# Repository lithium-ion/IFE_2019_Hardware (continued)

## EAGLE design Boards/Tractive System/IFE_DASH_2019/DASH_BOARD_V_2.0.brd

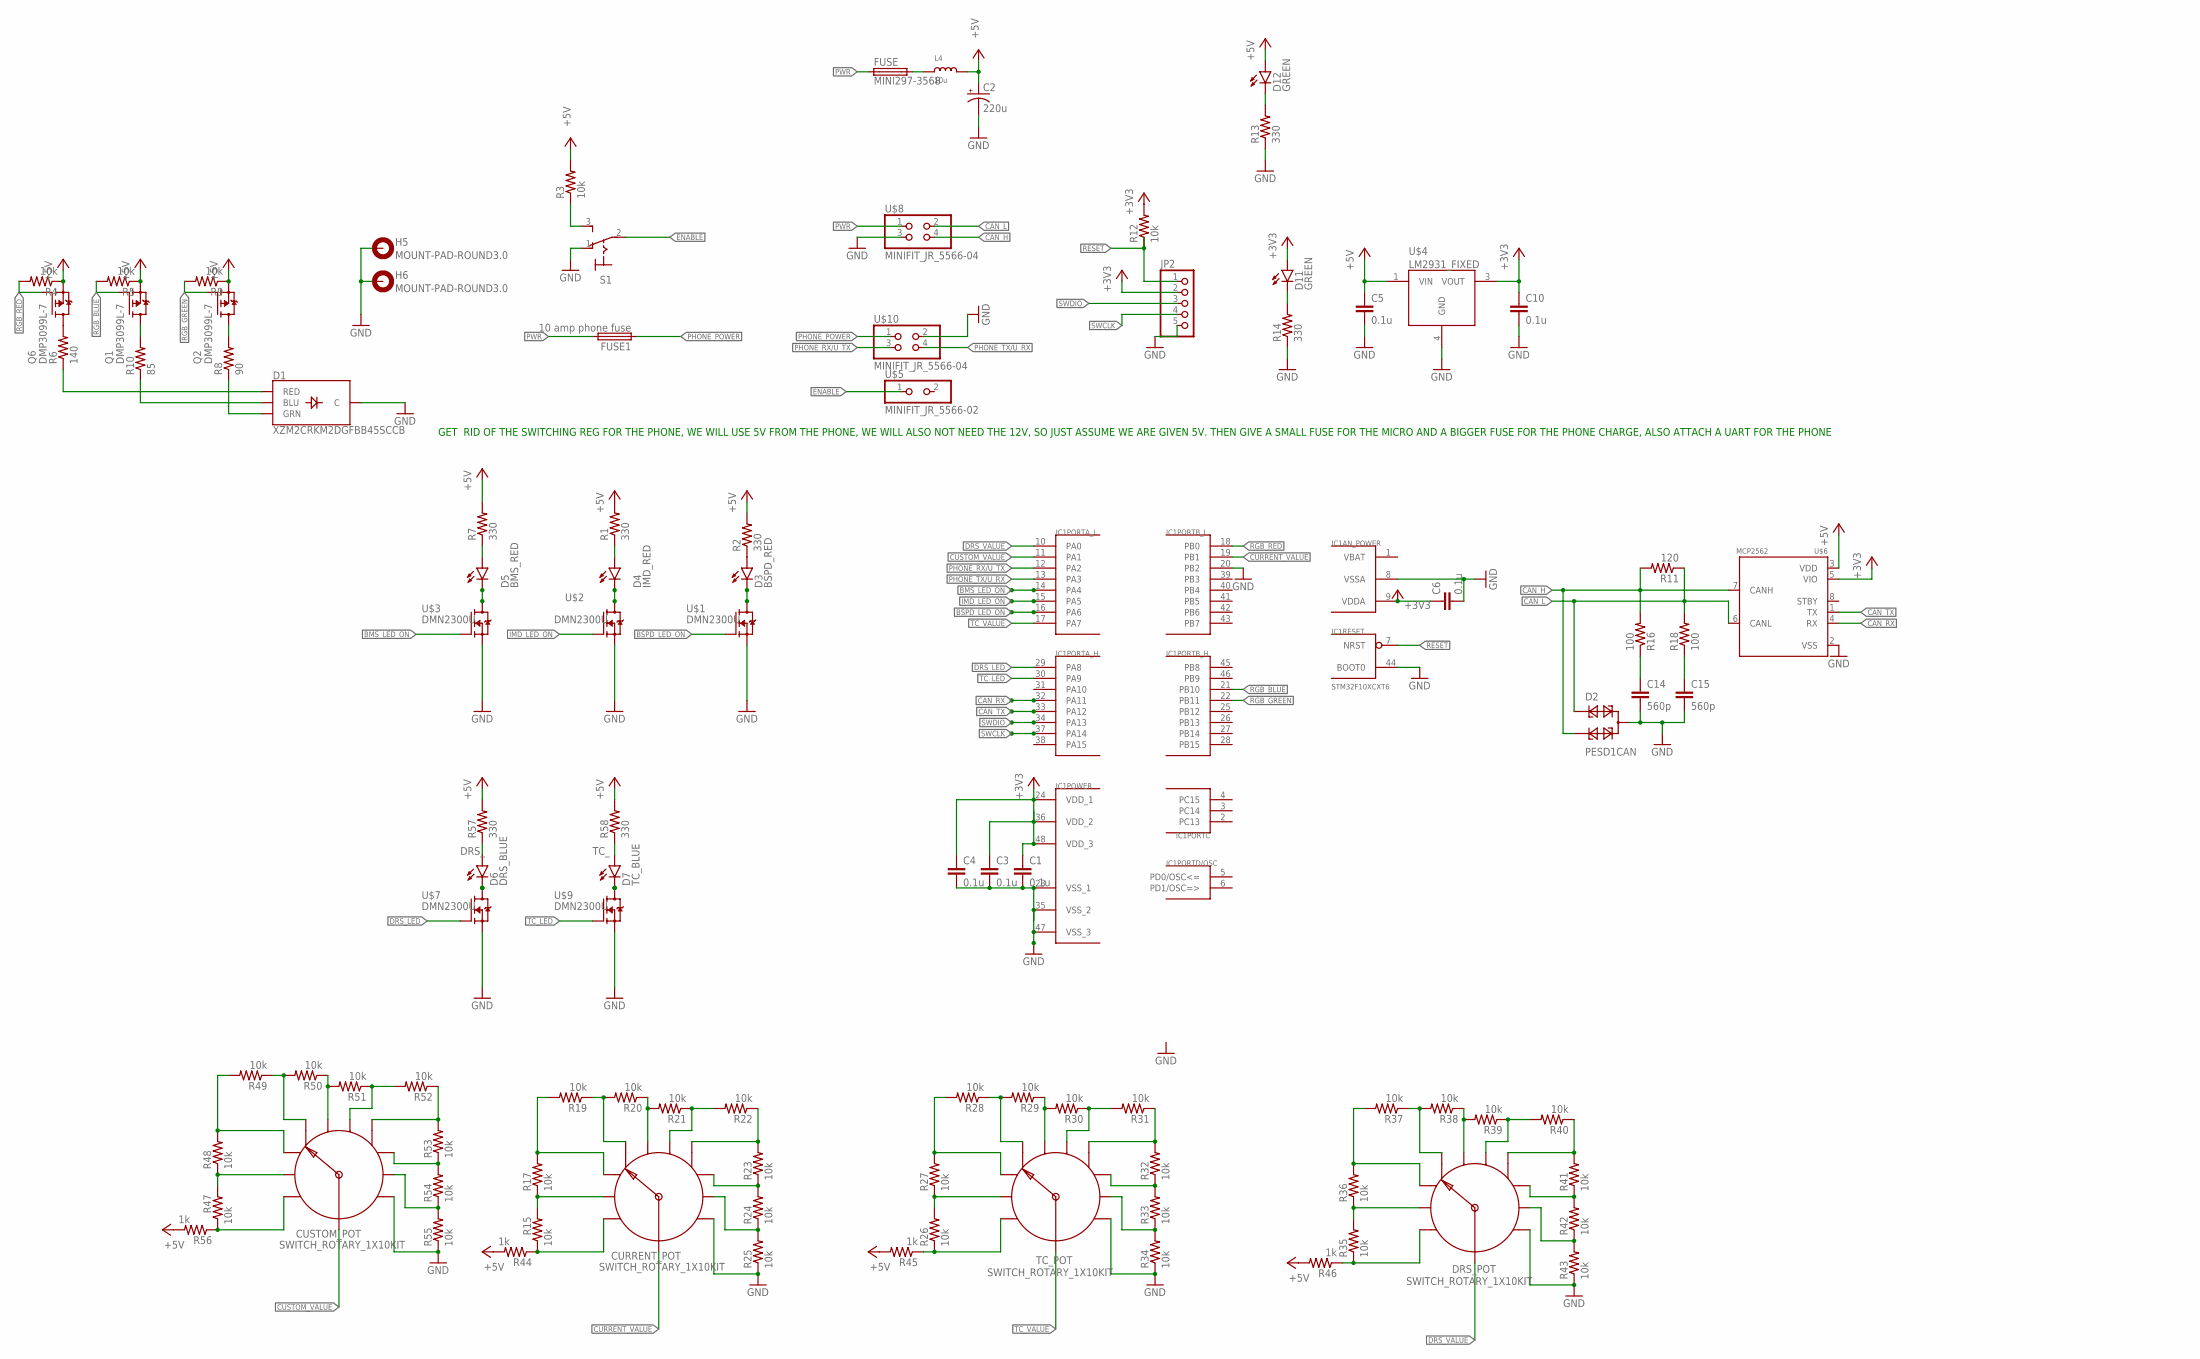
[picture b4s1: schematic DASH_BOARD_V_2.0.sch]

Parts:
C1, C3, C4, C5, C6, C10: 0.1u; C0805K
C2: 220u; E2,5-7
C14, C15: 560p; C0805K
CURRENT_POT: SWITCH_ROTARY_1X10KIT; ROTARY_SWITCH_1X10_KIT
CUSTOM_POT: SWITCH_ROTARY_1X10KIT; ROTARY_SWITCH_1X10_KIT
D1: XZM2CRKM2DGFBB45SCCB; PLCC4SMDLED
D2: PESD1CAN; SOT23
D3: BSPD_RED; LED-0603
D4: IMD_RED; LED-0603
D5: BMS_RED; LED-0603
D6: DRS_BLUE; LED-0603
D7: TC_BLUE; LED-0603
D11, D12: GREEN; LED-0603
DRS_POT: SWITCH_ROTARY_1X10KIT; ROTARY_SWITCH_1X10_KIT
FUSE: MINI297-3568; 3568
FUSE1: 10 amp phone fuse; 3568
H5, H6: MOUNT-PAD-ROUND3.0; 3,0-PAD
IC1: STM32F10XCXT6; TQFP48
JP2: PINHD-1X5; 1X05
L4: 10u; INDUCTOR_5X5MM_NR5040_NOTHERMALS
Q1, Q2, Q6: DMP3099L-7; SOT23
R1, R2, R7, R57, R58: 330; R0805
R3, R4, R5, R9, R12, R15, R17, R19, R20, R21, R22, R23, R24, R25, R26, R27, R28, R29, R30, R31, R32, R33, R34, R35, R36, R37, R38, R39, R40, R41, R42, R43, R47, R48, R49, R50, R51, R52, R53, R54, R55: 10k; R0805
R6: 140; R0805
R8: 90; R0805
R10: 85; R0805
R11: 120; R0805
R13, R14: 330; R0603
R16, R18: 100; R0805
R44, R45, R46, R56: 1k; R0805
S1: 320-916
TC_POT: SWITCH_ROTARY_1X10KIT; ROTARY_SWITCH_1X10_KIT
U$1, U$2, U$3, U$7, U$9: DMN2300U; SOT23
U$4: LM2931_FIXED; DPAK
U$5: MINIFIT_JR_5566-02
U$6: MCP2562; SOIC8
U$8, U$10: MINIFIT_JR_5566-04

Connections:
+3V3: C1.1, C3.1, C4.1, C6.1, C10.1, D11.A, IC1.9 (VDDA), IC1.24 (VDD_1), IC1.36 (VDD_2), IC1.48 (VDD_3), JP2.2, R12.2, U$4.3 (VOUT), U$6.5 (VIO)
+5V: C2.+, C5.1, D12.A, L4.P$2 (2), Q1.2 (S), Q2.2 (S), Q6.2 (S), R1.2, R2.2, R3.2, R4.1, R5.1, R7.2, R9.1, R44.2, R45.2, R46.2, R56.2, R57.2, R58.2, U$4.1 (VIN), U$6.3 (VDD)
BMS_LED: D5.A, R7.1
BMS_LED_ON: IC1.14 (PA4), U$3.1 (G)
BSPD_LED: D3.A, R2.1
BSPD_LED_ON: IC1.16 (PA6), U$1.1 (G)
CAN_H: D2.2, R11.2, R16.2, U$6.7 (CANH), U$8.4
CAN_L: D2.1, R11.1, R18.2, U$6.6 (CANL), U$8.2
CAN_RX: IC1.32 (PA11), U$6.4 (RX)
CAN_TX: IC1.33 (PA12), U$6.1 (TX)
CURRENT_VALUE: CURRENT_POT.COMMON, IC1.19 (PB1)
CUSTOM_VALUE: CUSTOM_POT.COMMON, IC1.11 (PA1)
DRS_: D6.A, R57.1
DRS_LED: IC1.29 (PA8), U$7.1 (G)
DRS_VALUE: DRS_POT.COMMON, IC1.10 (PA0)
ENABLE: S1.2, U$5.1
GND: C1.2, C2.-, C3.2, C4.2, C5.2, C6.2, C10.2, C14.2, C15.2, CURRENT_POT.10, CUSTOM_POT.10, D1.4 (C), D2.3, DRS_POT.10, H5.B3,0, H6.B3,0, IC1.8 (VSSA), IC1.20 (PB2), IC1.23 (VSS_1), IC1.35 (VSS_2), IC1.44 (BOOT0), IC1.47 (VSS_3), JP2.5, R13.1, R14.1, R25.1, R34.1, R43.1, R55.1, S1.1 (O), TC_POT.10, U$1.2 (S), U$2.2 (S), U$3.2 (S), U$4.4 (GND), U$6.2 (VSS), U$7.2 (S), U$8.3, U$9.2 (S), U$10.2
IMD_LED: D4.A, R1.1
IMD_LED_ON: IC1.15 (PA5), U$2.1 (G)
unnamed: Q6.3 (D), R6.2
unnamed: C14.1, R16.1
unnamed: D5.C, U$3.3 (D)
unnamed: R3.1, S1.3 (S)
unnamed: D1.2 (GRN), R8.1
unnamed: FUSE.P$2 (2), FUSE.P$3 (2), L4.P$1 (1)
unnamed: CURRENT_POT.2, R15.2, R17.1
unnamed: D4.C, U$2.3 (D)
unnamed: C15.1, R18.1
unnamed: D12.C, R13.2
unnamed: D11.C, R14.2
unnamed: D3.C, U$1.3 (D)
unnamed: CURRENT_POT.3, R17.2, R19.2
unnamed: CURRENT_POT.1, R15.1, R44.1
unnamed: D1.3 (BLU), R10.1
unnamed: D1.1 (RED), R6.1
unnamed: CURRENT_POT.4, R19.1, R20.2
unnamed: CURRENT_POT.5, R20.1, R21.2
unnamed: CURRENT_POT.6, R21.1, R22.2
unnamed: CURRENT_POT.7, R22.1, R23.2
unnamed: CURRENT_POT.8, R23.1, R24.2
unnamed: CURRENT_POT.9, R24.1, R25.2
unnamed: R26.1, R45.1, TC_POT.1
unnamed: Q1.3 (D), R10.2
unnamed: R26.2, R27.1, TC_POT.2
unnamed: R27.2, R28.2, TC_POT.3
unnamed: Q2.3 (D), R8.2
unnamed: R28.1, R29.2, TC_POT.4
unnamed: R29.1, R30.2, TC_POT.5
unnamed: R30.1, R31.2, TC_POT.6
unnamed: R31.1, R32.2, TC_POT.7
unnamed: R32.1, R33.2, TC_POT.8
unnamed: R33.1, R34.2, TC_POT.9
unnamed: CUSTOM_POT.2, R47.2, R48.1
unnamed: CUSTOM_POT.3, R48.2, R49.2
unnamed: DRS_POT.2, R35.2, R36.1
unnamed: DRS_POT.3, R36.2, R37.2
unnamed: DRS_POT.1, R35.1, R46.1
unnamed: DRS_POT.4, R37.1, R38.2
unnamed: DRS_POT.5, R38.1, R39.2
unnamed: DRS_POT.6, R39.1, R40.2
unnamed: DRS_POT.7, R40.1, R41.2
unnamed: DRS_POT.8, R41.1, R42.2
unnamed: DRS_POT.9, R42.1, R43.2
unnamed: CUSTOM_POT.4, R49.1, R50.2
unnamed: CUSTOM_POT.5, R50.1, R51.2
unnamed: CUSTOM_POT.6, R51.1, R52.2
unnamed: CUSTOM_POT.7, R52.1, R53.2
unnamed: CUSTOM_POT.8, R53.1, R54.2
unnamed: CUSTOM_POT.9, R54.1, R55.2
unnamed: CUSTOM_POT.1, R47.1, R56.1
unnamed: D6.C, U$7.3 (D)
unnamed: D7.C, U$9.3 (D)
PHONE_POWER: FUSE1.P$1 (1), FUSE1.P$4 (1), U$10.1
PHONE_RX/U_TX: IC1.12 (PA2), U$10.3
PHONE_TX/U_RX: IC1.13 (PA3), U$10.4
PWR: FUSE.P$1 (1), FUSE.P$4 (1), FUSE1.P$2 (2), FUSE1.P$3 (2), U$8.1
RESET: IC1.7 (NRST), JP2.1, R12.1
RGB_BLUE: IC1.21 (PB10), Q1.1 (G), R5.2
RGB_GREEN: IC1.22 (PB11), Q2.1 (G), R9.2
RGB_RED: IC1.18 (PB0), Q6.1 (G), R4.2
SWCLK: IC1.37 (PA14), JP2.4
SWDIO: IC1.34 (PA13), JP2.3
TC_: D7.A, R58.1
TC_LED: IC1.30 (PA9), U$9.1 (G)
TC_VALUE: IC1.17 (PA7), TC_POT.COMMON
VBAT: IC1.1 (VBAT)

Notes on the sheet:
GET RID OF THE SWITCHING REG FOR THE PHONE, WE WILL USE 5V FROM THE PHONE, WE WILL ALSO NOT NEED THE 12V, SO JUST ASSUME WE ARE GIVEN 5V. THEN GIVE A SMALL FUSE FOR THE MICRO AND A BIGGER FUSE FOR THE PHONE CHARGE, ALSO ATTACH A UART FOR THE PHONE

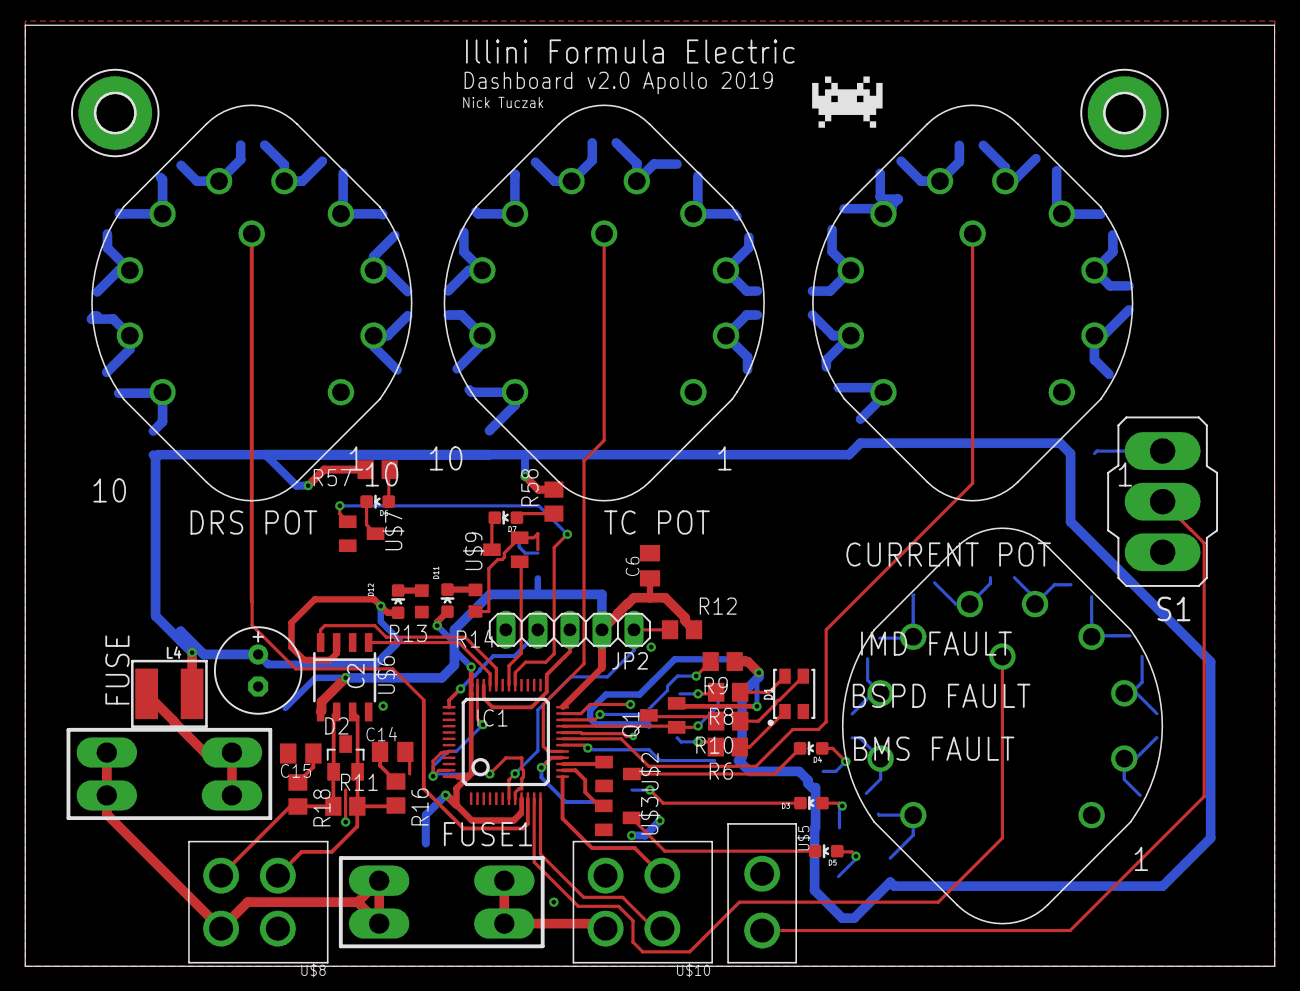
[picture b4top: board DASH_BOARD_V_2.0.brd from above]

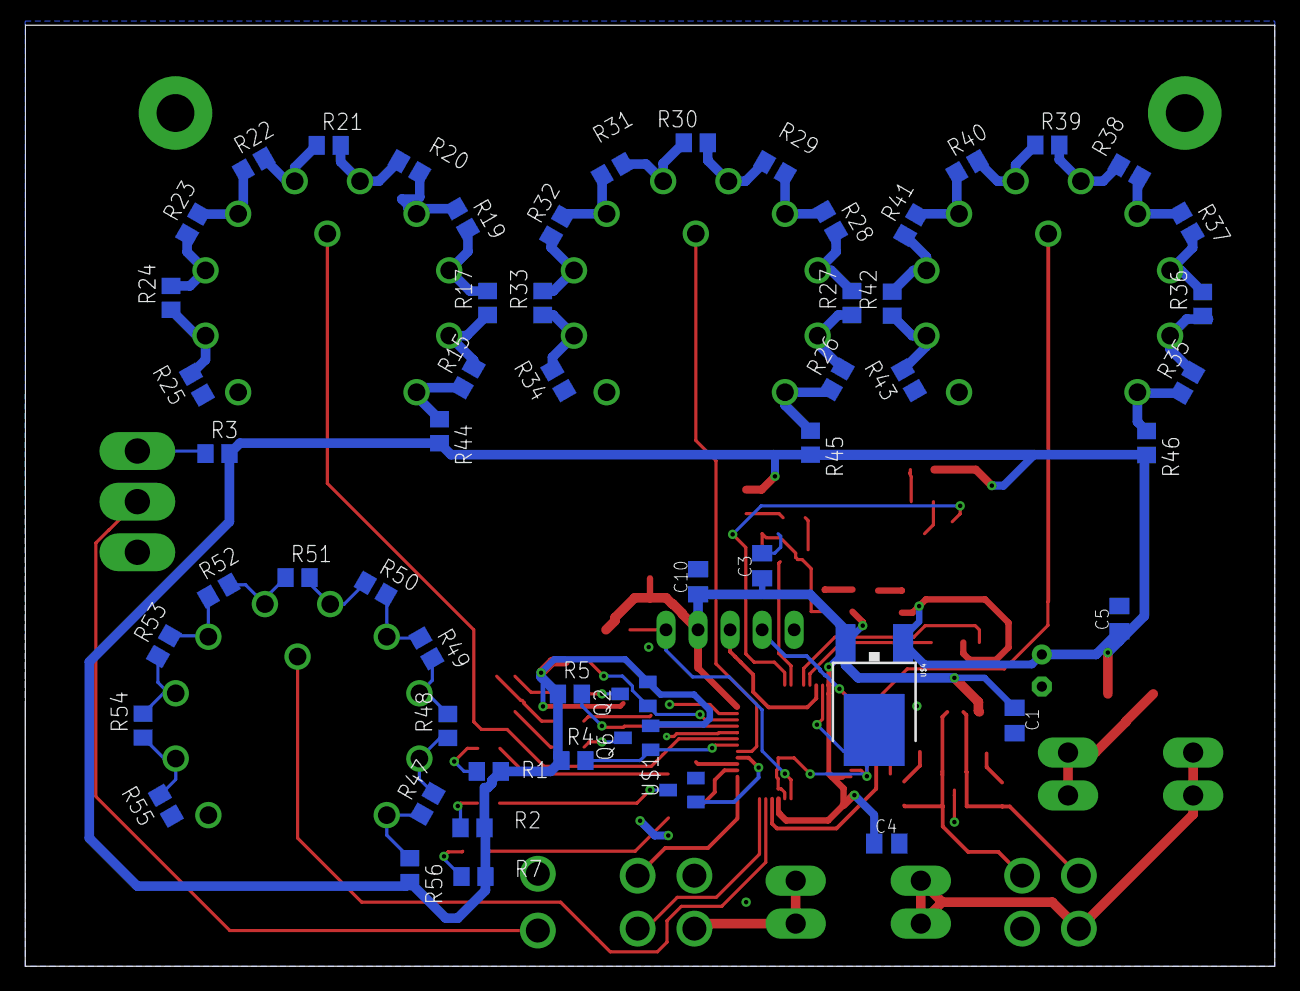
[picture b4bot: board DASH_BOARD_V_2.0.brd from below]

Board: 2 copper layers, 99.1 x 74.6 mm, 101 parts (55 on the bottom side), 85 nets.

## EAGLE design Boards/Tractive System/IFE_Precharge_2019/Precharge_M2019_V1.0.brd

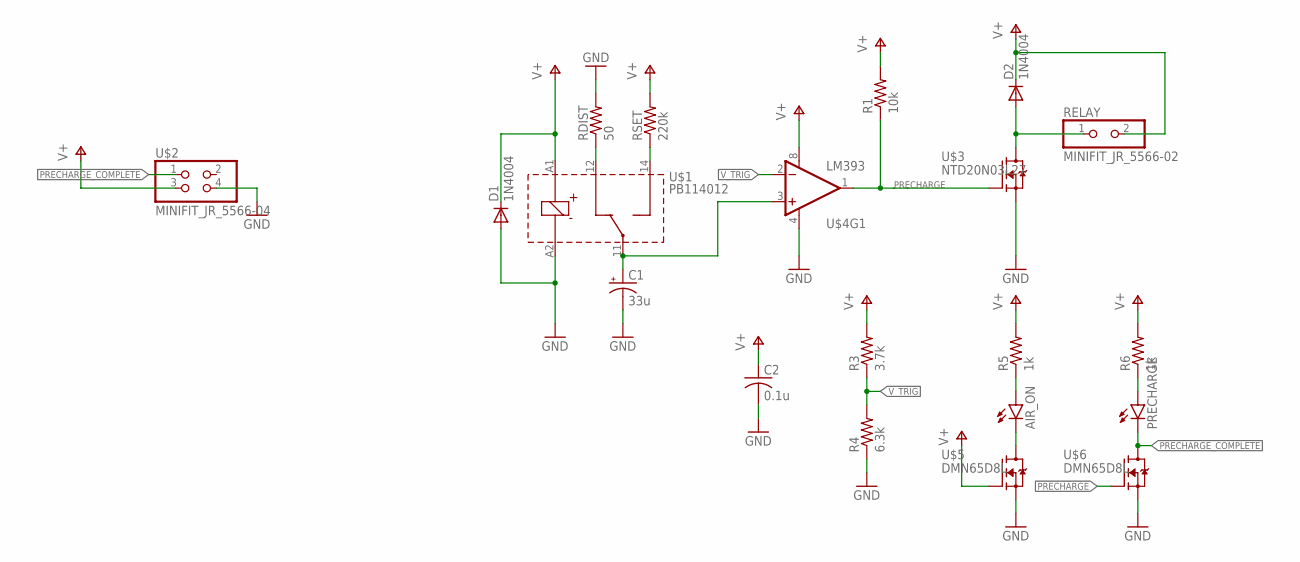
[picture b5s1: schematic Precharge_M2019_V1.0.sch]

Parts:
AIR_ON: LED0603; LED-0603
C1: 33u; E2,5-5
C2: 0.1u; C0805
D1, D2: 1N4004; DO41-10
PRECHARGE: LED0603; LED-0603
R1: 10k; R0805
R3: 3.7k; R0805
R4: 6.3k; R0805
R5, R6: 1k; R0805
RDIST: 50; AXIAL-0.5
RELAY: MINIFIT_JR_5566-02
RSET: 220k; 0207/10
U$1: PB114012; TH_SPDT_MINI_POWER_RELAY_PB
U$2: MINIFIT_JR_5566-04
U$3: NTD20N03L27; DPACK
U$4: LM393; SO08
U$5, U$6: DMN65D8L; SOT23

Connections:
GND: C1.-, C2.2, D1.A, R4.1, RDIST.P$2 (2), U$1.A2 (COIL-), U$2.4, U$3.3 (S), U$4.4 (V-), U$5.2 (S), U$6.2 (S)
unnamed: RSET.1, U$1.14 (NO)
unnamed: C1.+, U$1.11 (COM), U$4.3 (+IN)
unnamed: RDIST.P$1 (1), U$1.12 (NC)
unnamed: D2.A, RELAY.1, U$3.2 (D)
unnamed: AIR_ON.A, R5.1
unnamed: PRECHARGE.A, R6.1
unnamed: AIR_ON.C, U$5.3 (D)
PRECHARGE: R1.1, U$3.1 (G), U$4.1 (OUT), U$6.1 (G)
PRECHARGE_COMPLETE: PRECHARGE.C, U$2.1, U$6.3 (D)
V+: C2.1, D1.C, D2.C, R1.2, R3.2, R5.2, R6.2, RELAY.2, RSET.2, U$1.A1 (COIL+), U$2.3, U$4.8 (V+), U$5.1 (G)
V_TRIG: R3.1, R4.2, U$4.2 (-IN)

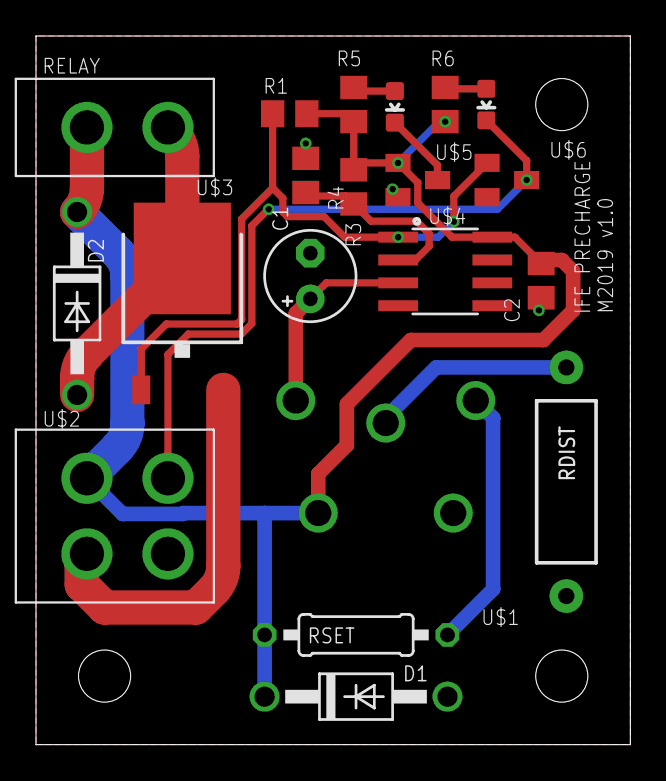
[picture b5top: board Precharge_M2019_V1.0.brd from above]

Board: 2 copper layers, 33.0 x 39.4 mm, 20 parts (0 on the bottom side), 12 nets.

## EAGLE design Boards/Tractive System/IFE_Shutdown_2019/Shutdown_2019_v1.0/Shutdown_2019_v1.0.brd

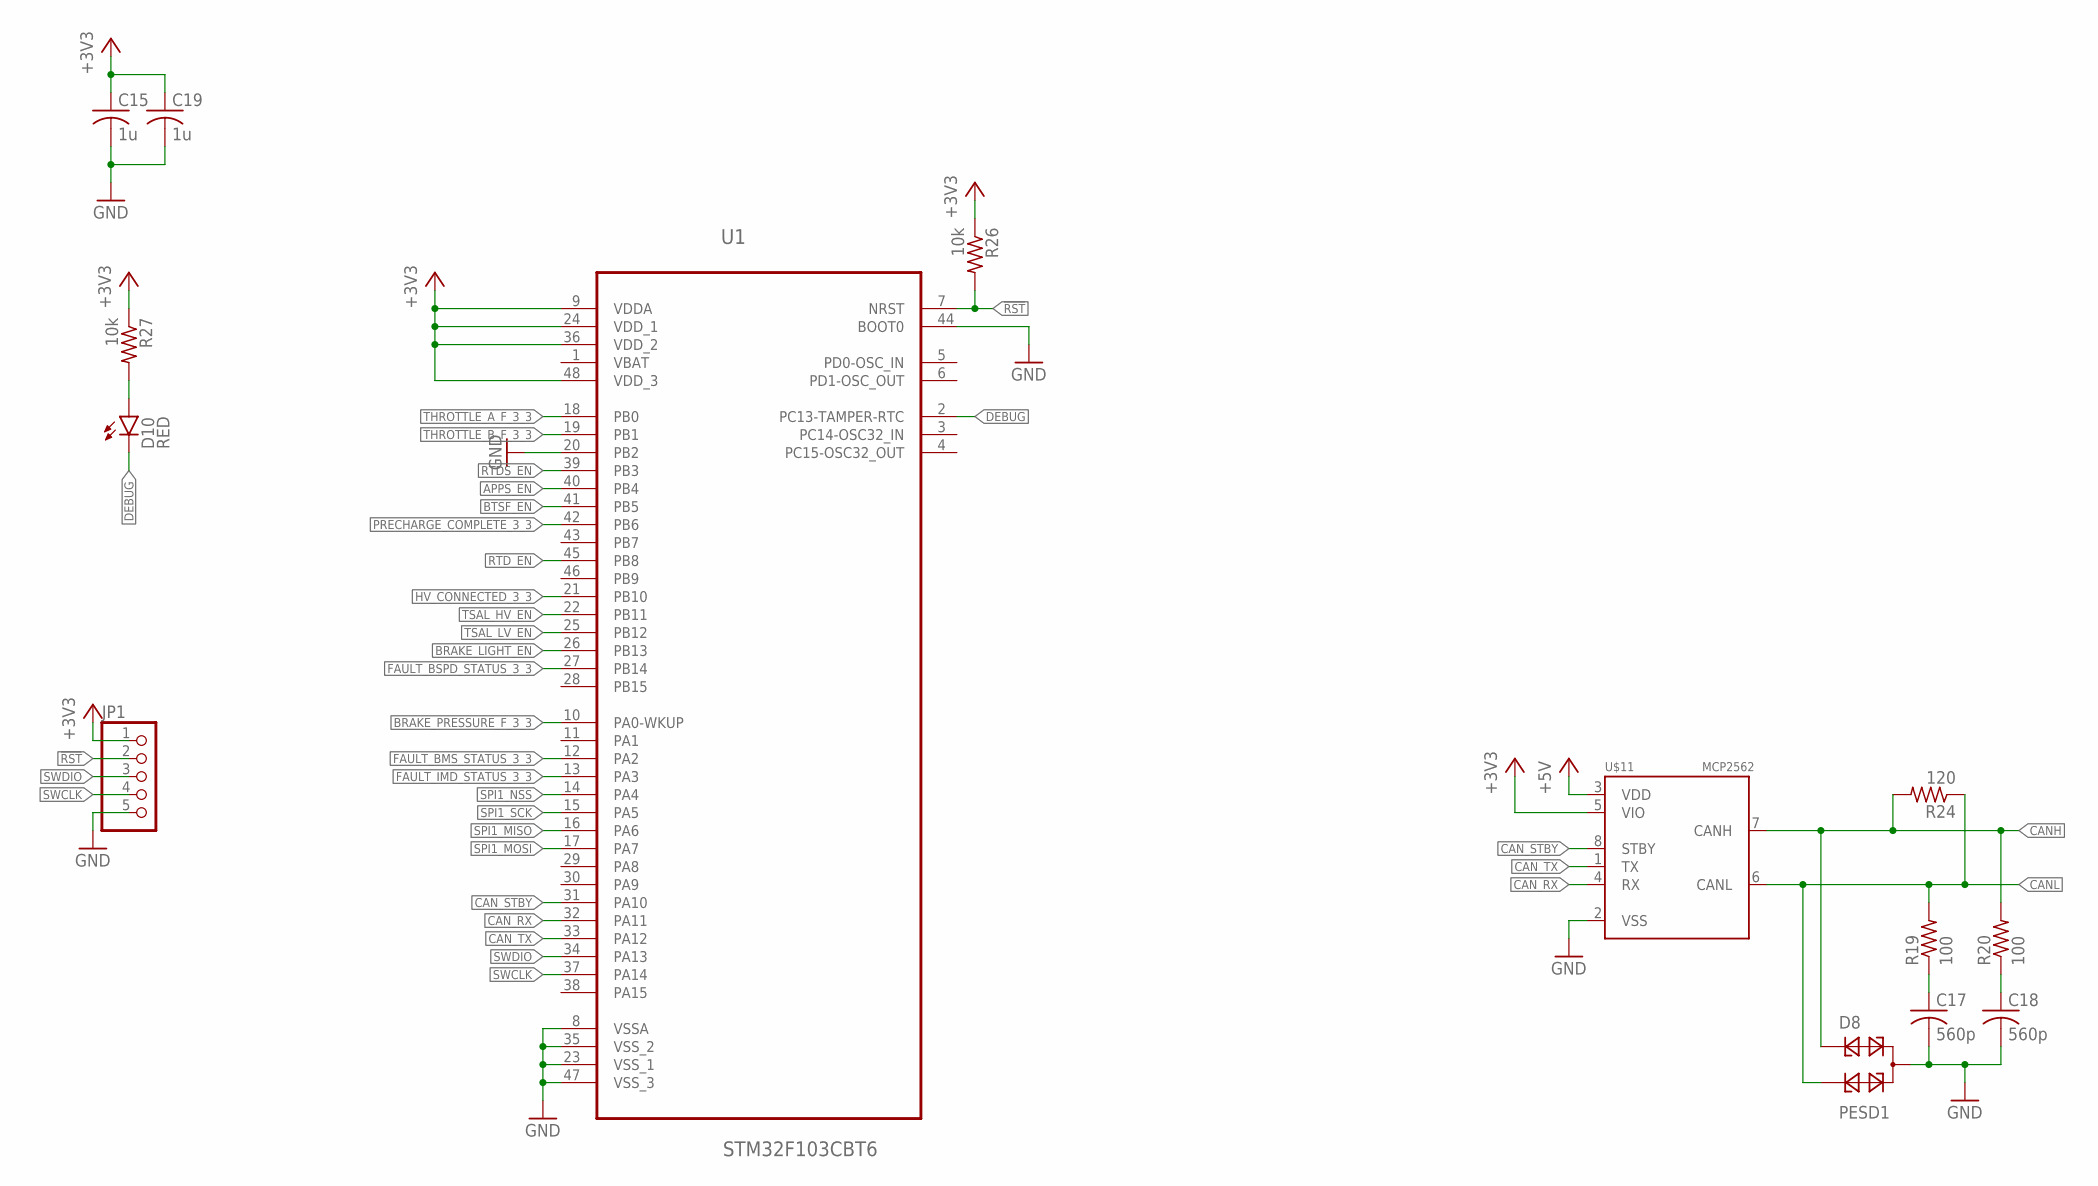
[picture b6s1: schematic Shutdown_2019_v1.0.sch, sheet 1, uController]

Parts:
C15, C19: 1u; C0805
C17, C18: 560p; C0603
D8: PESD1; SOT23
D10: RED; LED-0603
JP1: PINHD-1X5; 1X05
R19, R20: 100; R0603
R24: 120; R0603
R26, R27: 10k; R0603
U1: STM32F103CBT6; QFP50P900X900X160-48N
U$11: MCP2562; SOIC8

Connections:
!RST: JP1.2, R26.2, U1.7 (NRST)
+3V3: C15.1, C19.1, JP1.1, R26.1, R27.1, U1.9 (VDDA), U1.24 (VDD_1), U1.36 (VDD_2), U1.48 (VDD_3), U$11.5 (VIO); also elsewhere on the board
+5V: U$11.3 (VDD); also elsewhere on the board
APPS_EN: U1.40 (PB4); also elsewhere on the board
BRAKE_LIGHT_EN: U1.26 (PB13); also elsewhere on the board
BRAKE_PRESSURE_F_3_3: U1.10 (PA0-WKUP); also elsewhere on the board
BTSF_EN: U1.41 (PB5); also elsewhere on the board
CANH: D8.1, R20.2, R24.2, U$11.7 (CANH); also elsewhere on the board
CANL: D8.2, R19.2, R24.1, U$11.6 (CANL); also elsewhere on the board
CAN_RX: U1.32 (PA11), U$11.4 (RX)
CAN_STBY: U1.31 (PA10), U$11.8 (STBY)
CAN_TX: U1.33 (PA12), U$11.1 (TX)
DEBUG: D10.C, U1.2 (PC13-TAMPER-RTC)
FAULT_BMS_STATUS_3_3: U1.12 (PA2); also elsewhere on the board
FAULT_BSPD_STATUS_3_3: U1.27 (PB14); also elsewhere on the board
FAULT_IMD_STATUS_3_3: U1.13 (PA3); also elsewhere on the board
GND: C15.2, C17.2, C18.2, C19.2, D8.3, JP1.5, U1.8 (VSSA), U1.20 (PB2), U1.23 (VSS_1), U1.35 (VSS_2), U1.44 (BOOT0), U1.47 (VSS_3), U$11.2 (VSS); also elsewhere on the board
HV_CONNECTED_3_3: U1.21 (PB10); also elsewhere on the board
unnamed: C17.1, R19.1
unnamed: C18.1, R20.1
unnamed: D10.A, R27.2
PRECHARGE_COMPLETE_3_3: U1.42 (PB6); also elsewhere on the board
RTDS_EN: U1.39 (PB3); also elsewhere on the board
RTD_EN: U1.45 (PB8); also elsewhere on the board
SPI1_MISO: U1.16 (PA6); also elsewhere on the board
SPI1_MOSI: U1.17 (PA7); also elsewhere on the board
SPI1_NSS: U1.14 (PA4); also elsewhere on the board
SPI1_SCK: U1.15 (PA5); also elsewhere on the board
SWCLK: JP1.4, U1.37 (PA14)
SWDIO: JP1.3, U1.34 (PA13)
THROTTLE_A_F_3_3: U1.18 (PB0); also elsewhere on the board
THROTTLE_B_F_3_3: U1.19 (PB1); also elsewhere on the board
TSAL_HV_EN: U1.22 (PB11); also elsewhere on the board
TSAL_LV_EN: U1.25 (PB12); also elsewhere on the board

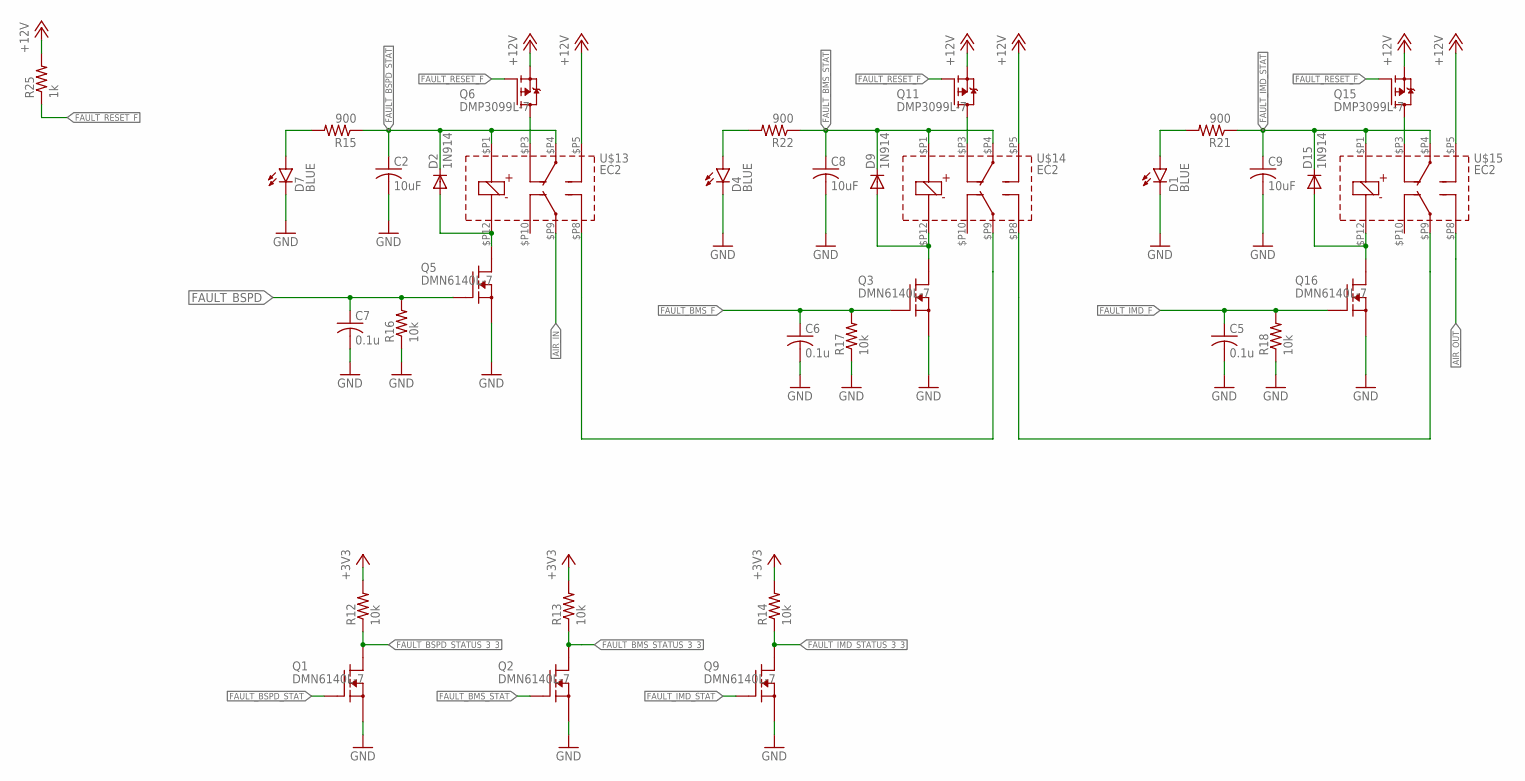
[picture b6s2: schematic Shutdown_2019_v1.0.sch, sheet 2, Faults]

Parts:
C2, C8, C9: 10uF; C0805
C5, C6, C7: 0.1u; C0603
D1, D4, D7: BLUE; LED-0603
D2, D9, D15: 1N914; SOD323-F
Q1, Q2, Q3, Q5, Q9, Q16: DMN6140L-7; SOT23
Q6, Q11, Q15: DMP3099L-7; SOT23
R12, R13, R14, R16, R17, R18: 10k; R0603
R15, R21, R22: 900; R0603
R25: 1k; R0603
U$13, U$14, U$15: EC2; DPDT_2.54

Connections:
+3V3: R12.2, R13.2, R14.2; also elsewhere on the board
+12V: Q6.2 (S), Q11.2 (S), Q15.2 (S), R25.2, U$13.$P5, U$14.$P5, U$15.$P5; also elsewhere on the board
AIR_IN: U$13.$P9; also elsewhere on the board
AIR_OUT: U$15.$P8; also elsewhere on the board
FAULT_BMS_F: C6.1, Q3.1 (G), R17.2; also elsewhere on the board
FAULT_BMS_STAT: C8.1, D9.C, Q2.1 (G), R22.1, U$14.$P1, U$14.$P4
FAULT_BMS_STATUS_3_3: Q2.3 (D), R13.1; also elsewhere on the board
FAULT_BSPD: C7.1, Q5.1 (G), R16.2; also elsewhere on the board
FAULT_BSPD_STAT: C2.1, D2.C, Q1.1 (G), R15.1, U$13.$P1, U$13.$P4
FAULT_BSPD_STATUS_3_3: Q1.3 (D), R12.1; also elsewhere on the board
FAULT_IMD_F: C5.1, Q16.1 (G), R18.2; also elsewhere on the board
FAULT_IMD_STAT: C9.1, D15.C, Q9.1 (G), R21.1, U$15.$P1, U$15.$P4
FAULT_IMD_STATUS_3_3: Q9.3 (D), R14.1; also elsewhere on the board
FAULT_RESET_F: Q6.1 (G), Q11.1 (G), Q15.1 (G), R25.1; also elsewhere on the board
GND: C2.2, C5.2, C6.2, C7.2, C8.2, C9.2, D1.C, D4.C, D7.C, Q1.2 (S), Q2.2 (S), Q3.2 (S), Q5.2 (S), Q9.2 (S), Q16.2 (S), R16.1, R17.1, R18.1; also elsewhere on the board
unnamed: D9.A, Q3.3 (D), U$14.$P12
unnamed: D7.A, R15.2
unnamed: U$13.$P8, U$14.$P9
unnamed: Q6.3 (D), U$13.$P3
unnamed: U$14.$P8, U$15.$P9
unnamed: D2.A, Q5.3 (D), U$13.$P12
unnamed: D4.A, R22.2
unnamed: Q11.3 (D), U$14.$P3
unnamed: D1.A, R21.2
unnamed: Q15.3 (D), U$15.$P3
unnamed: D15.A, Q16.3 (D), U$15.$P12

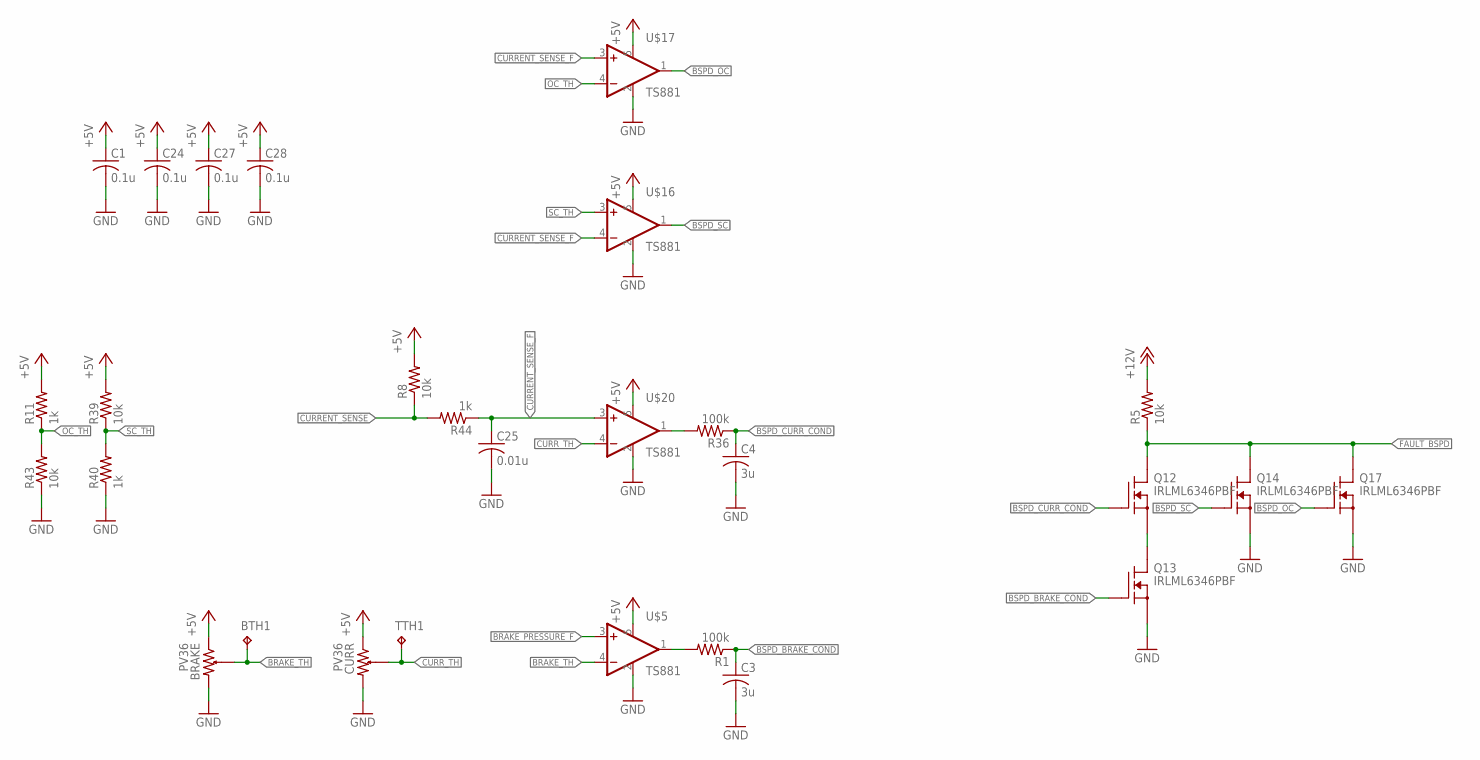
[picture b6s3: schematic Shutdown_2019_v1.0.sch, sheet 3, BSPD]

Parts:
BRAKE: PV36
BTH1: TPTP09R; TP09R
C1, C24, C27, C28: 0.1u; C0603
C3, C4: 3u; C0603
C25: 0.01u; C0603
CURR: PV36
Q12, Q13, Q14, Q17: IRLML6346PBF; SOT23
R1, R36: 100k; R0603
R5, R8, R39, R43: 10k; R0603
R11, R40, R44: 1k; R0603
TTH1: TPTP09R; TP09R
U$5, U$16, U$17, U$20: TS881; SOT23-5

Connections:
+5V: BRAKE.A, C1.1, C24.1, C27.1, C28.1, CURR.A, R8.2, R11.2, R39.2, U$5.5 (VDD), U$16.5 (VDD), U$17.5 (VDD), U$20.5 (VDD); also elsewhere on the board
+12V: R5.2; also elsewhere on the board
BRAKE_PRESSURE_F: U$5.3 (+IN); also elsewhere on the board
BRAKE_TH: BRAKE.W, BTH1.TP, U$5.4 (-IN)
BSPD_BRAKE_COND: C3.1, Q13.1 (G), R1.1
BSPD_CURR_COND: C4.1, Q12.1 (G), R36.1
BSPD_OC: Q17.1 (G), U$17.1 (OUT)
BSPD_SC: Q14.1 (G), U$16.1 (OUT)
CURRENT_SENSE: R8.1, R44.2; also elsewhere on the board
CURRENT_SENSE_F: C25.1, R44.1, U$16.4 (-IN), U$17.3 (+IN), U$20.3 (+IN)
CURR_TH: CURR.W, TTH1.TP, U$20.4 (-IN)
FAULT_BSPD: Q12.3 (D), Q14.3 (D), Q17.3 (D), R5.1; also elsewhere on the board
GND: BRAKE.B, C1.2, C3.2, C4.2, C24.2, C25.2, C27.2, C28.2, CURR.B, Q13.2 (S), Q14.2 (S), Q17.2 (S), R40.1, R43.1, U$5.2 (GND), U$16.2 (GND), U$17.2 (GND), U$20.2 (GND); also elsewhere on the board
unnamed: Q12.2 (S), Q13.3 (D)
unnamed: R36.2, U$20.1 (OUT)
unnamed: R1.2, U$5.1 (OUT)
OC_TH: R11.1, R43.2, U$17.4 (-IN)
SC_TH: R39.1, R40.2, U$16.3 (+IN)

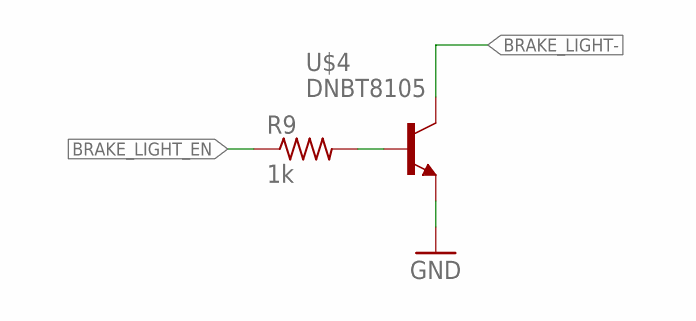
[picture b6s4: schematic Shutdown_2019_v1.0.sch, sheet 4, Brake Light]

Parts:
R9: 1k; R0603
U$4: DNBT8105; SOT23-3

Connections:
BRAKE_LIGHT-: U$4.3 (C); also elsewhere on the board
BRAKE_LIGHT_EN: R9.1; also elsewhere on the board
GND: U$4.2 (E); also elsewhere on the board
unnamed: R9.2, U$4.1 (B)

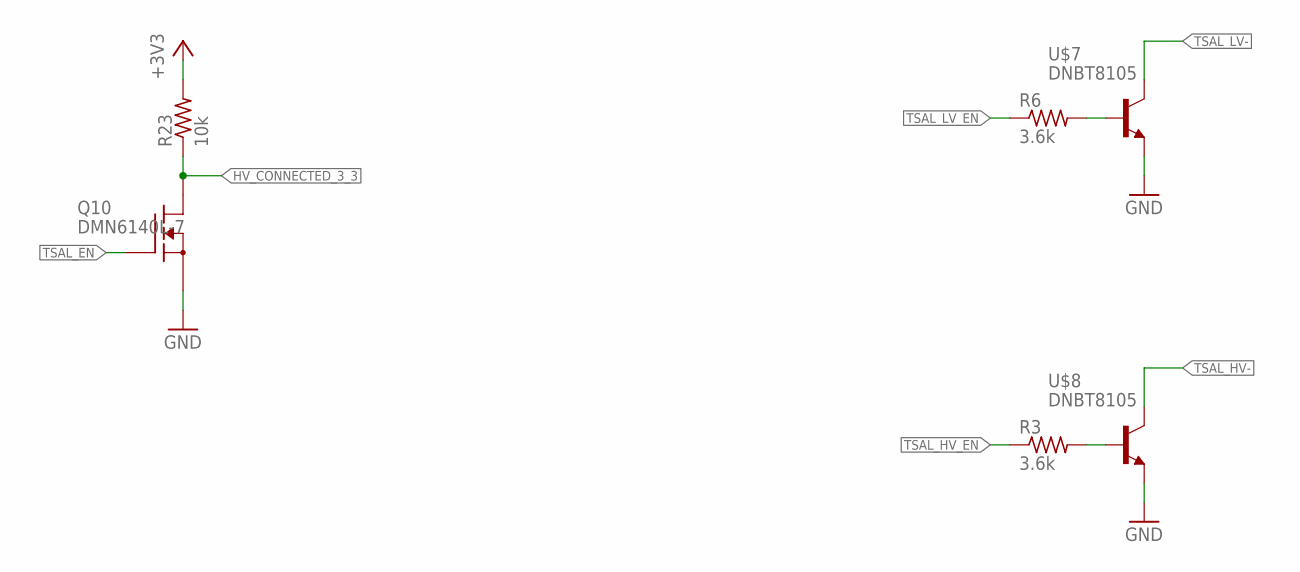
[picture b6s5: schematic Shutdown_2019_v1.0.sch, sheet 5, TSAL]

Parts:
Q10: DMN6140L-7; SOT23
R3, R6: 3.6k; R0603
R23: 10k; R0603
U$7, U$8: DNBT8105; SOT23-3

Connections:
+3V3: R23.2; also elsewhere on the board
GND: Q10.2 (S), U$7.2 (E), U$8.2 (E); also elsewhere on the board
HV_CONNECTED_3_3: Q10.3 (D), R23.1; also elsewhere on the board
unnamed: R3.2, U$8.1 (B)
unnamed: R6.2, U$7.1 (B)
TSAL_EN: Q10.1 (G); also elsewhere on the board
TSAL_HV-: U$8.3 (C); also elsewhere on the board
TSAL_HV_EN: R3.1; also elsewhere on the board
TSAL_LV-: U$7.3 (C); also elsewhere on the board
TSAL_LV_EN: R6.1; also elsewhere on the board

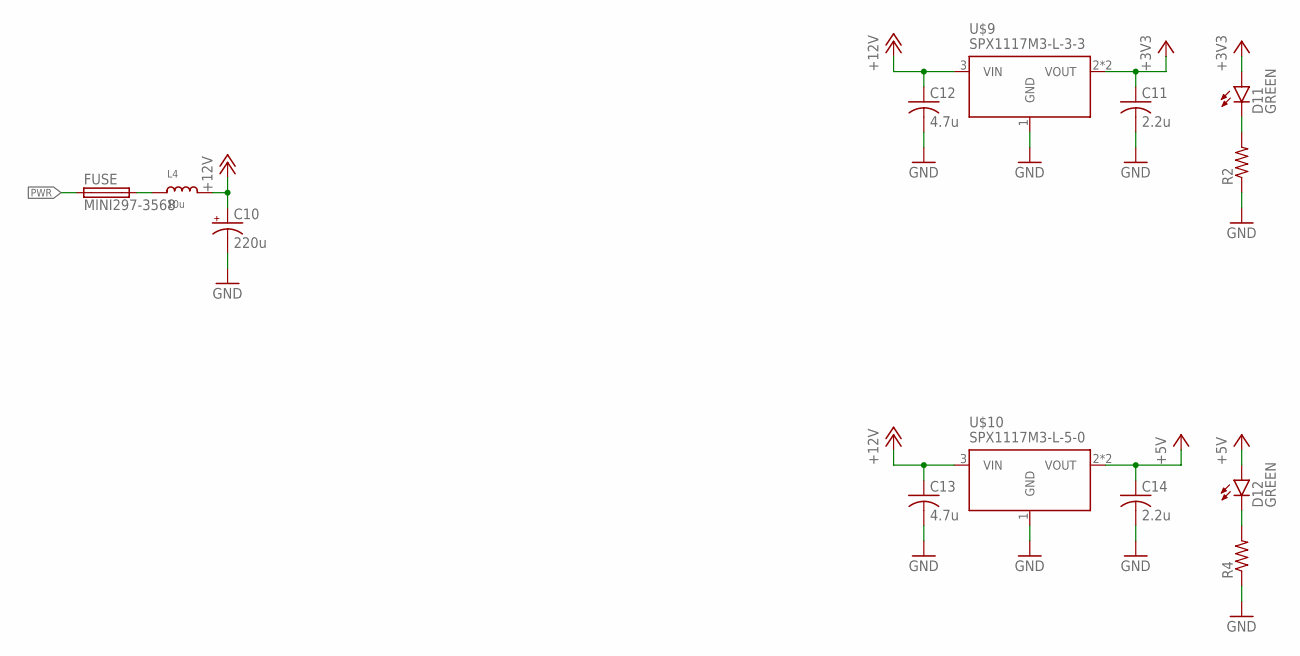
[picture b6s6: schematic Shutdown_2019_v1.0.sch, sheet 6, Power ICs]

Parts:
C10: 220u; E2,5-7
C11, C14: 2.2u; C0805
C12, C13: 4.7u; C0805
D11, D12: GREEN; LED-0603
FUSE: MINI297-3568; 3568
L4: 10u; INDUCTOR_5X5MM_NR5040_NOTHERMALS
R2, R4: R-US_R0603; R0603
U$9: SPX1117M3-L-3-3; SOT223
U$10: SPX1117M3-L-5-0; SOT223

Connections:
+3V3: C11.1, D11.A, U$9.2 (VOUT), U$9.4 (VOUT); also elsewhere on the board
+5V: C14.1, D12.A, U$10.2 (VOUT), U$10.4 (VOUT); also elsewhere on the board
+12V: C10.+, C12.1, C13.1, L4.P$2 (2), U$9.3 (VIN), U$10.3 (VIN); also elsewhere on the board
GND: C10.-, C11.2, C12.2, C13.2, C14.2, R2.1, R4.1, U$9.1 (GND), U$10.1 (GND); also elsewhere on the board
unnamed: FUSE.P$2 (2), FUSE.P$3 (2), L4.P$1 (1)
unnamed: D12.C, R4.2
unnamed: D11.C, R2.2
PWR: FUSE.P$1 (1), FUSE.P$4 (1); also elsewhere on the board
